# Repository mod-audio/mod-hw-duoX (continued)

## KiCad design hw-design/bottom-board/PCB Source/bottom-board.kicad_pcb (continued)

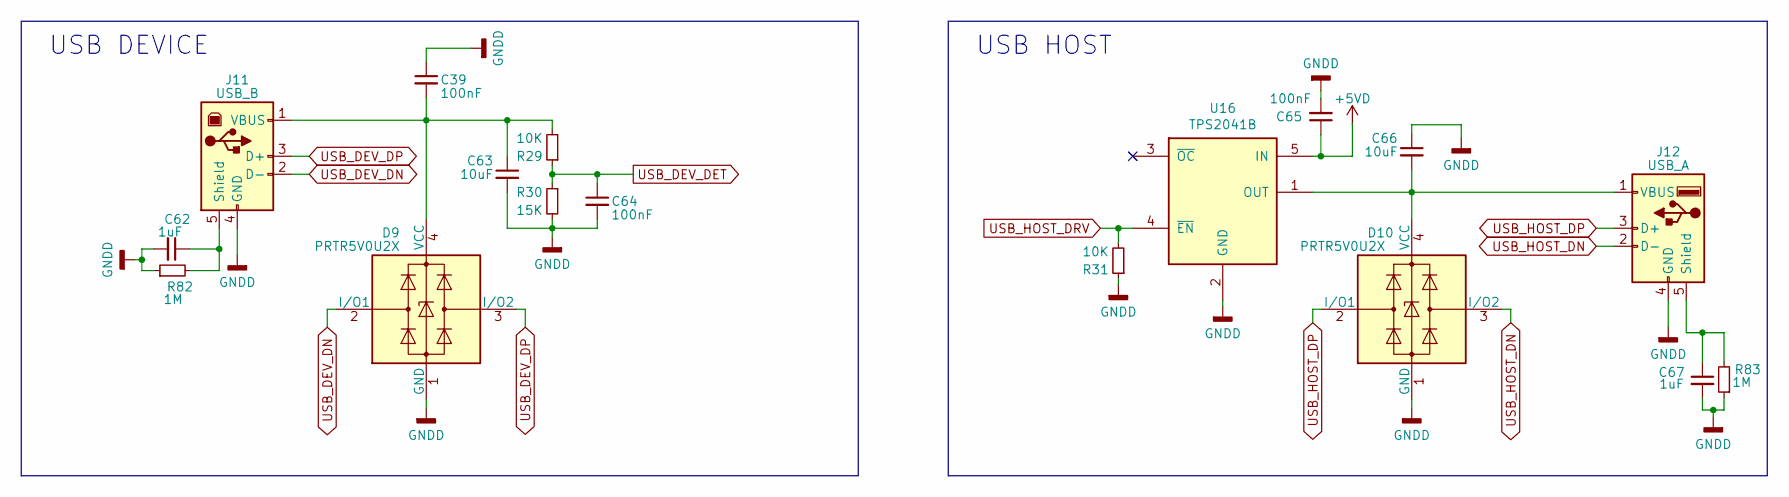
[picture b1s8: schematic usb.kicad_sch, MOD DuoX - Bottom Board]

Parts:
C39, C64, C65: 100nF; C_0603_1608Metric; MPN GCM188R71C104KA37D
C62, C67: 1uF; C_0603_1608Metric; MPN TMK107B7105KA-T
C63, C66: 10uF; C_0805_2012Metric; MPN GRM219R61E106KA12D
D9, D10: PRTR5V0U2X; SOT-143; MPN PRTR5V0U2X,215
J11: USB_B; USB_B_OST_USB-B1HSxx_Horizontal; MPN 61729-1011BLF
J12: USB_A; USB_A_Vertical; MPN KUSBX-SLAS1N-B
R29, R31: 10K; R_0603_1608Metric; MPN RR0816P-103-D
R30: 15K; R_0603_1608Metric; MPN RMCF0603JT15K0
R82, R83: 1M; R_0603_1608Metric; MPN RT0603BRD071ML
U16: TPS2041B; SOT-23-5

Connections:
+5VD: C65.1, U16.5 (IN); also elsewhere on the board
GNDD: C39.1, C62.2, C63.2, C64.2, C65.2, C66.1, C67.2, D9.1 (GND), D10.1 (GND), J11.4 (GND), J12.4 (GND), R30.2, R31.1, R82.1, R83.1, U16.2 (GND); also elsewhere on the board
unnamed: C39.2, C63.1, D9.4 (VCC), J11.1 (VBUS), R29.2
unnamed: C62.1, J11.5 (Shield), R82.2
unnamed: C66.2, D10.4 (VCC), J12.1 (VBUS), U16.1 (OUT)
unnamed: C67.1, J12.5 (Shield), R83.2
USB_DEV_DET: C64.1, R29.1, R30.1; also elsewhere on the board
USB_DEV_DN: D9.2 (I/O1), J11.2 (D-); also elsewhere on the board
USB_DEV_DP: D9.3 (I/O2), J11.3 (D+); also elsewhere on the board
USB_HOST_DN: D10.3 (I/O2), J12.2 (D-); also elsewhere on the board
USB_HOST_DP: D10.2 (I/O1), J12.3 (D+); also elsewhere on the board
USB_HOST_DRV: R31.2, U16.4 (~EN); also elsewhere on the board

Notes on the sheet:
USB DEVICE
USB HOST

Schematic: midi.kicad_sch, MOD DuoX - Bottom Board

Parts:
C68: 100nF; C_0603_1608Metric; MPN GCM188R71C104KA37D
D11, D12: 1N4148; D_SOD-323; MPN 1N4148WX-TP
D28: BAT54S; SOT-23; MPN BAT54SFILM
J13, J14: DIN_5; SDS-50J; MPN SDS-50J
Q3, Q4: 2N7002; SOT-23; MPN 2N7002P,215
R32, R33, R34: 220R; R_0603_1608Metric; MPN RC0603FR-07220RL
R35, R36: 10K; R_0603_1608Metric; MPN RR0816P-103-D
U17: 6N136S; SMDIP-8_W9.53mm; MPN 6N136S

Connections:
+5VD: C68.2, D28.2, R33.2, R35.1, R36.1, U17.8; also elsewhere on the board
GNDD: C68.1, D28.1, J14.2, Q3.2 (S), Q4.2 (S), U17.5; also elsewhere on the board
MIDI_UART_RX: D12.2 (A); also elsewhere on the board
MIDI_UART_TX: Q4.1 (G); also elsewhere on the board
unnamed: D11.1 (K), R32.2, U17.2
unnamed: D11.2 (A), J13.5, U17.3
unnamed: D12.1 (K), U17.6
unnamed: D28.3, J14.5, R34.1
unnamed: J13.4, R32.1
unnamed: J14.4, R33.1
unnamed: Q3.1 (G), Q4.3 (D), R36.2
unnamed: Q3.3 (D), R34.2, R35.2

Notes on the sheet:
MIDI IN
MIDI OUT
Opto: If = 16mA, Vf = 1.4V

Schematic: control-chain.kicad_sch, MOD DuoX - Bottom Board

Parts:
C69: 10uF; C_0805_2012Metric; MPN GRM219R61E106KA12D
C70, C71: 100nF; C_0603_1608Metric; MPN GCM188R71C104KA37D
J4: RJ45; Ethernet_Jack_54602-908LF; MPN 54602-908LF
R37, R38: 22R; R_0603_1608Metric; MPN RMCF0603JT22R0
R39, R40: 10K; R_0603_1608Metric; MPN RR0816P-103-D
R43, R44, R45, R46: 56R; R_0603_1608Metric; MPN CRGCQ0603F56R
R47: 100R; R_0603_1608Metric; MPN RT0603DRD07100RL
U18: ISL83086E; SOIC-14_3.9x8.7mm_P1.27mm; MPN ISL83491IBZ

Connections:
+5VD: C71.1, R39.1, U18.13 (VCC), U18.14 (VCC); also elsewhere on the board
+12V: C69.1, C70.1, J4.4, J4.5; also elsewhere on the board
CHAIN_UART_DE: R40.1, U18.4 (DE); also elsewhere on the board
CHAIN_UART_RE: R39.2, U18.3 (~RE); also elsewhere on the board
CHAIN_UART_RX: R38.1; also elsewhere on the board
CHAIN_UART_TX: R37.1; also elsewhere on the board
GNDD: C69.2, C70.2, C71.2, J4.7, J4.8, R40.2, U18.6 (GND), U18.7 (GND); also elsewhere on the board
unnamed: R37.2, U18.5 (DI)
unnamed: R38.2, U18.2 (RO)
unnamed: R43.2, U18.12 (A)
unnamed: R44.2, U18.11 (~B)
unnamed: R45.2, U18.9 (Y)
unnamed: R46.2, U18.10 (~Z)
RS485_RX+: J4.3, R43.1, R47.1
RS485_RX-: J4.6, R44.1, R47.2
RS485_TX+: J4.1, R45.1
RS485_TX-: J4.2, R46.1

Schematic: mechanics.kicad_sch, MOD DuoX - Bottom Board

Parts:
FID1, FID2, FID3: FIDUCIAL; fiducial_in-circuit
H1, H2, H3, H4, H5: HOLE; MountingHole_3.5mm
H6, H7: Standoff; MountingHole_3.2mm_M3_DIN965_Pad; MPN 9774030243R
H8, H9: HOLE; MountingHole_2.7mm
IMG1: Logo; mod-logo

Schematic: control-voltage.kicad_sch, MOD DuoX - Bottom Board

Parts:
C34, C35, C76, C81: 10uF; C_0805_2012Metric; MPN GRM219R61E106KA12D
C73, C74: 33nF; C_0603_1608Metric; MPN C0603C333K4RACTU
C75, C80, C82, C83: 100nF; C_0603_1608Metric; MPN GCM188R71C104KA37D
C77: 1uF; C_0603_1608Metric; MPN TMK107B7105KA-T
D13, D20: 1N4148; D_SOD-323; MPN 1N4148WX-TP
D14, D15: BAT54S; SOT-23; MPN BAT54SFILM
J16, J17: NYS215; NMJ6HCD2; MPN NYS215
R48, R50, R51, R52, R79, R80, R133, R134, R135, R136, R137, R138, R139, R140: 10K; R_0603_1608Metric; MPN RR0816P-103-D
R85: 56K; R_0603_1608Metric; MPN RT0603DRD0756KL
R86: 100K; R_0603_1608Metric; MPN RMCF0603JT100K
R87: 220K; R_0603_1608Metric; MPN RMCF0603JT220K
R88: 47K; R_0603_1608Metric; MPN RMCF0603JT47K0
R89, R90: 15K; R_0603_1608Metric; MPN RMCF0603JT15K0
R141, R142: 499K; R_0603_1608Metric; MPN ERJ-3EKF4993V
R143, R144: 1K; R_0603_1608Metric; MPN ERJ-PB3D1001V
TP14, TP15, TP16: TestPoint; TestPoint_Pad_D1.0mm
U3: 74LVC3G17; VSSOP-8_2.3x2mm_P0.5mm; MPN SN74LVC3G17DCUR
U4: LD1117S50TR; SOT-223-3_TabPin2; MPN LD1117S50TR
U9: DG9426E; TSSOP-16_4.4x5mm_P0.65mm
U10: LM358; TSSOP-8_3x3mm_P0.65mm; MPN TLV272CM8-13
U13: DG9426E; TSSOP-16_4.4x5mm_P0.65mm; MPN DG9426EDQ-T1-GE3
U20: ADC122S021; VSSOP-8_3.0x3.0mm_P0.65mm; MPN ADC122S021CIMM/NOPB
U21: MIC2076A; SOIC-8_3.9x4.9mm_P1.27mm; MPN MIC2076A-1YM
U24: MCP4922-EP; SOIC-14_3.9x8.7mm_P1.27mm; MPN MCP4922T-E/SL

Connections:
+5VA: C80.2, C81.1, C82.2, C83.2, R141.1, R142.1, U3.8 (VCC), U13.12 (VL), U24.1 (VDD), U24.9 (~SHDN), U24.11 (VrefB), U24.13 (VrefA); also elsewhere on the board
+5VP: C35.1, C75.2, C76.1, C77.2, D14.2, D15.2, R79.2, R80.2, R86.2, U4.2 (VO), U9.12 (VL), U20.2 (VA), U21.7 (IN); also elsewhere on the board
CV1_IN: J16.T, R133.1, U9.14, U21.8 (OUTA)
CV2_IN: J16.R, R134.1, U9.11, U21.5 (OUTB)
CV_10V_OUT1: R139.2, U10.1, U13.11
CV_10V_OUT2: R140.2, U10.7, U13.15
CV_ADC_DIN: U3.1, U20.6 (DIN); also elsewhere on the board
CV_ADC_DOUT: U20.7 (DOUT); also elsewhere on the board
CV_ADC_SCLK: U3.3, U20.8 (SCLK); also elsewhere on the board
CV_ADC_~CS~: TP16.1, U20.1 (~CS); also elsewhere on the board
CV_DAC_~CS~: U3.6; also elsewhere on the board
CV_EXP_SW: D13.1 (K), D20.1 (K), R48.1, U9.1, U9.8, U9.9, U9.16
CV_IN_DET: J16.SN, R85.2, R86.1; also elsewhere on the board
CV_OUT_1: R143.2, U10.3 (+)
CV_OUT_2: R144.2, U10.5 (+)
CV_OUT_DET: J17.SN, R87.1, R88.2; also elsewhere on the board
EXP_EN1: D13.2 (A), R51.1, TP15.1, U21.1 (ENA); also elsewhere on the board
EXP_EN2: D20.2 (A), R50.1, TP14.1, U21.4 (ENB); also elsewhere on the board
EXP_FLAG1: R80.1, R89.2, U21.2 (FLGA); also elsewhere on the board
EXP_FLAG2: R79.1, R90.2, U21.3 (FLGB); also elsewhere on the board
GNDD: C77.1, R48.2, R50.2, R51.2, R52.2, R85.1, R88.1, R89.1, R90.1, R135.2, R136.2, U9.4 (V-), U9.5 (GND), U13.4 (V-), U13.5 (GND), U21.6 (GND); also elsewhere on the board
HP_CV_JACK_RING: J17.R, U13.6, U13.14
HP_CV_JACK_TIP: J17.T, U13.3, U13.10
HP_DISABLE: R52.1, U13.1, U13.8, U13.9, U13.16; also elsewhere on the board
HP_LEFT: U13.2; also elsewhere on the board
HP_RIGHT: U13.7; also elsewhere on the board
unnamed: C73.1, D15.3, U9.2, U9.15, U20.5 (IN1)
unnamed: C74.1, D14.3, U9.7, U9.10, U20.4 (IN2)
unnamed: R133.2, R135.1, U9.3
unnamed: R134.2, R136.1, U9.6
unnamed: R137.2, R139.1, U10.2 (-)
unnamed: R138.2, R140.1, U10.6 (-)
unnamed: R141.2, R143.1, U24.14 (VoutA)
unnamed: R142.2, R144.1, U24.10 (VoutB)
unnamed: U3.2, U24.3 (~CS)
unnamed: U3.5, U24.4 (SCK)
unnamed: U3.7, U24.5 (SDI)

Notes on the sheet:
Overcurrent flag pullup
CV INPUT
DAC outputs have Hi-Z (500k) when shutdown is on
Exp. Pedal Enable
Amplify the signel by a factor of 2, to scale back to the 0 to 10V range Needs to be rail to rail with 10V as supply
MIC2076A outputs have Hi-Z when disabled
CV OUTPUT

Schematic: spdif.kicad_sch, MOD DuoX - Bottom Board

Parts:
C84: 10nF; C_0603_1608Metric; MPN CL10B103KA8NNNC
C85: 22pF; C_0603_1608Metric; MPN C0603C220K4GACTU
J18: MJ-3536N; MPN MJ-3536N
R55: 243R; R_0603_1608Metric; MPN RC0603FR-07243RL
R56: 107R; R_0603_1608Metric; MPN RC0603FR-07107RL
TR1: Transformer_1P_1S_SO8; PE-65812NL; MPN PE-65812NL

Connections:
CODEC_SPDIF_OUT: C84.2; also elsewhere on the board
GNDD: C85.1, R56.2, TR1.4 (AB); also elsewhere on the board
unnamed: C84.1, R55.2
unnamed: C85.2, J18.S, TR1.5 (SA)
unnamed: J18.T, TR1.8 (SB)
unnamed: R55.1, R56.1, TR1.1 (AA)

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
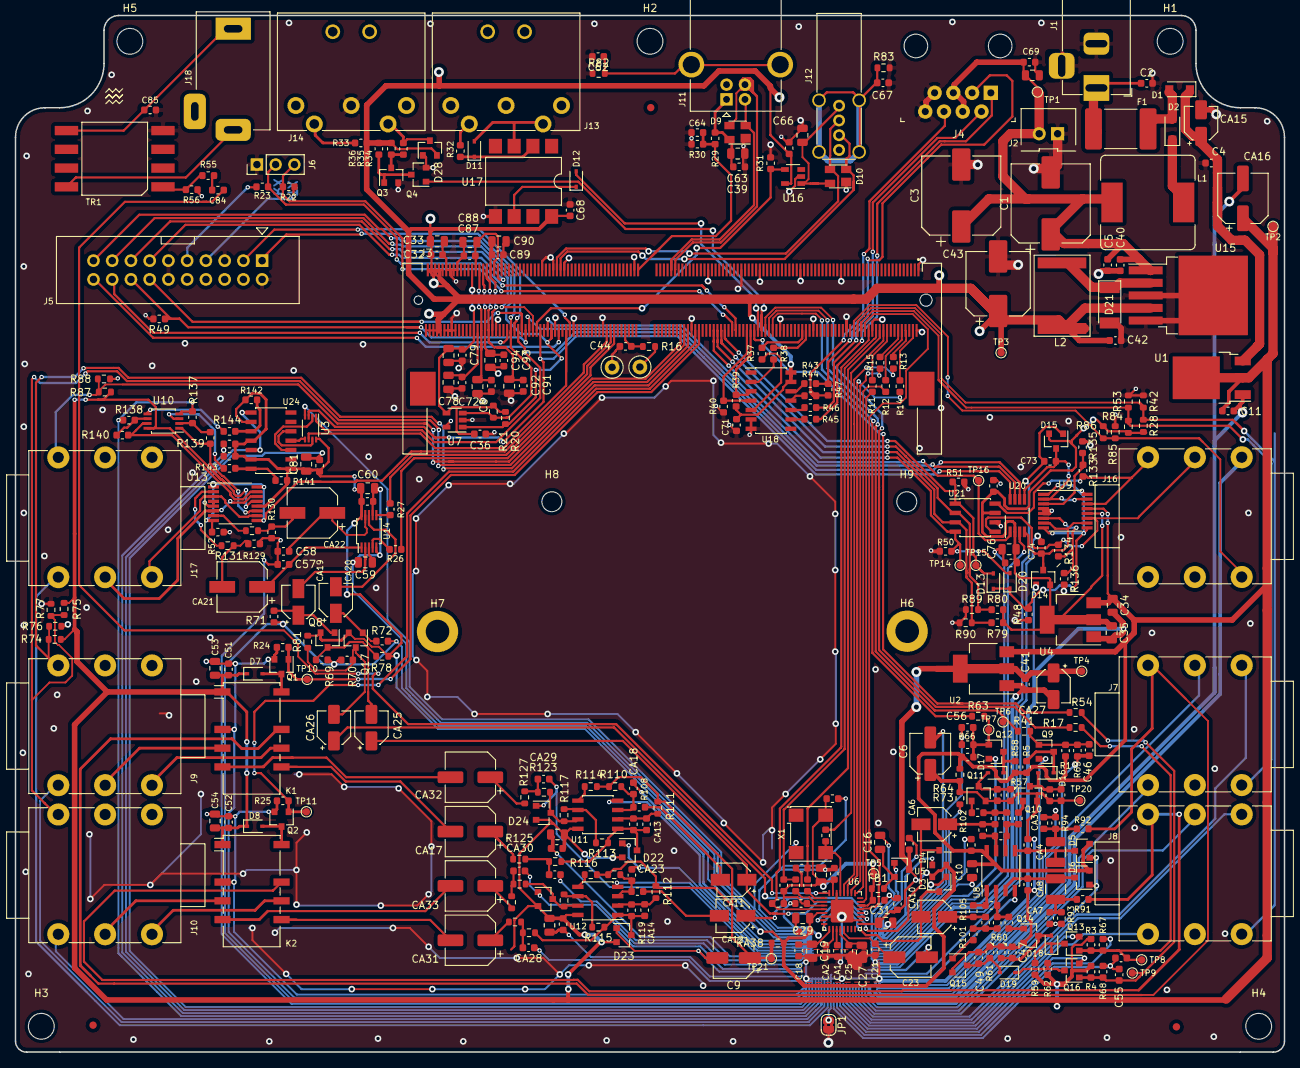
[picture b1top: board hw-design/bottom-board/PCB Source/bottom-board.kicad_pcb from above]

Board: 4 copper layers, 172.0 x 140.5 mm, 390 parts (1 on the bottom side), 227 nets.

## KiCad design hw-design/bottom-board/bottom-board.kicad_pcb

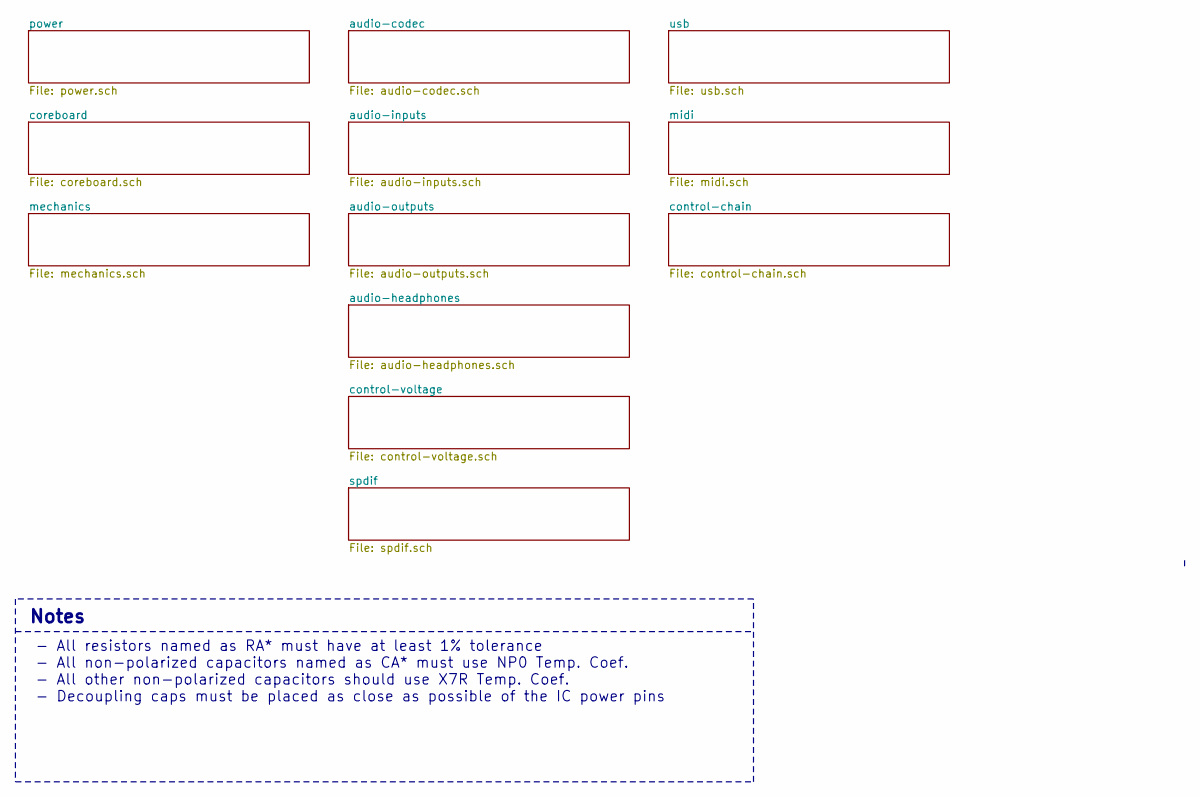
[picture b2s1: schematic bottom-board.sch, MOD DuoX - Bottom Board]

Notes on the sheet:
- All resistors named as RA* must have at least 1% tolerance - All non-polarized capacitors named as CA* must use NP0 Temp. Coef. - All other non-polarized capacitors should use X7R Temp. Coef. - Decoupling caps must be placed as close as possible of the IC power pins
Notes

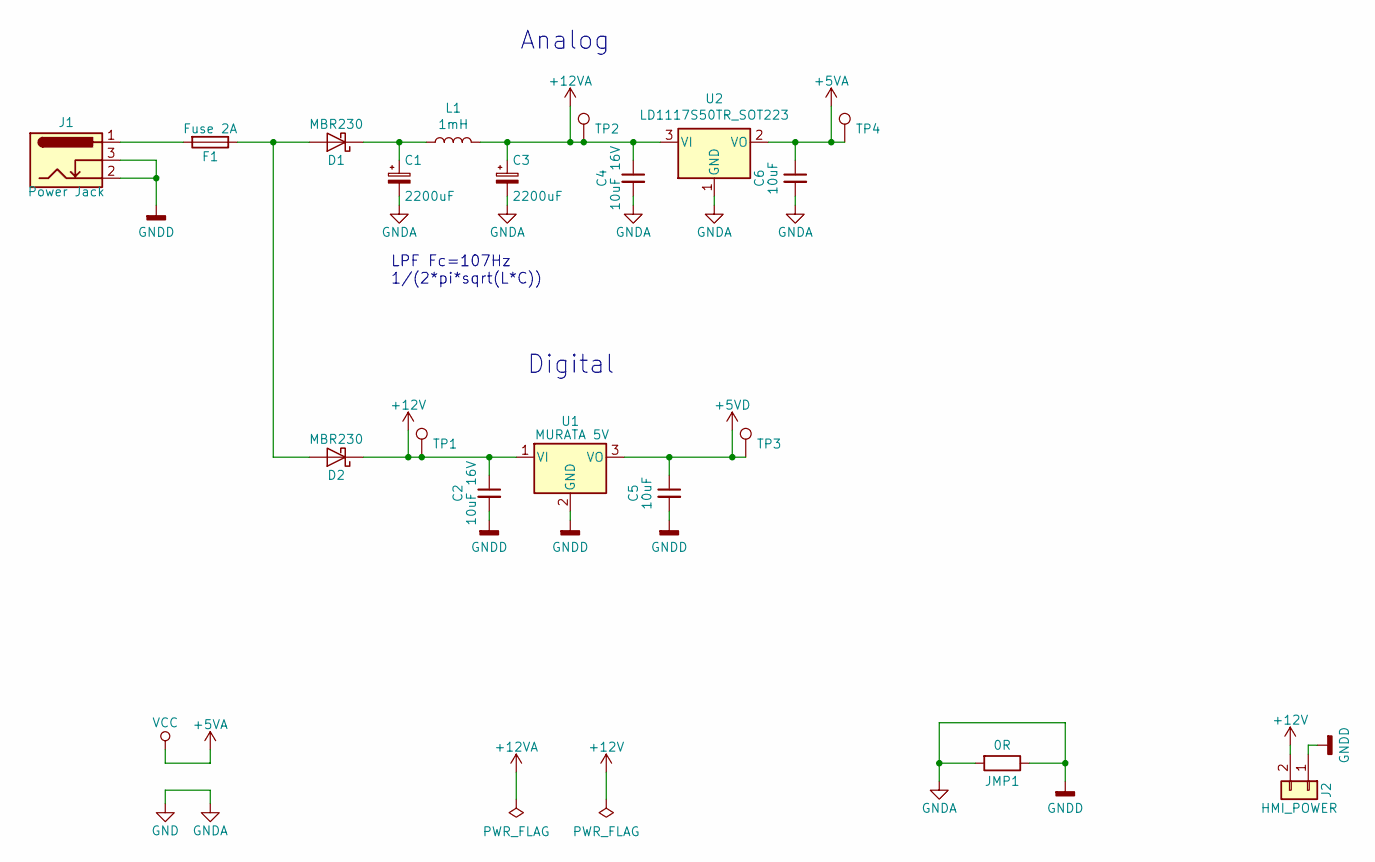
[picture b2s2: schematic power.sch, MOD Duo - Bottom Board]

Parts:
C1, C3: 2200uF; CP_Radial_D13.0mm_P5.00mm; MPN ESK228M025AL4AA
C2, C4: 10uF 16V; C_0805_2012Metric; MPN CL21A106KOFNNNE
C5, C6: 10uF; C_0603_1608Metric; MPN CL10A106MQ8NNNC
D1, D2: MBR230; D_SOD-123F; MPN MBR230LSFT1G
F1: Fuse 2A; Fuse_2920_0ZCF_Bel; MPN 0ZCF0200FF2C
J1: Power Jack; BarrelJack_Horizontal; MPN PJ-002AH
J2: HMI_POWER; B2B-XH-A; MPN B2B-XH-A(LF)(SN)
JMP1: 0R; Jumper_SMD_THT
L1: 1mH; L_Bourns_SRR1260; MPN SRR1260-102K
TP1, TP2, TP3, TP4: TestPoint; TestPoint_Pad_D1.0mm
U1: MURATA 5V; OKI-78SR_Vertical; MPN OKI-78SR-5/1.5-W36-C
U2: LD1117S50TR_SOT223; SOT-223-3_TabPin2; MPN LD1117S50TR

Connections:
+5VD: C5.1, TP3.1, U1.3 (VO); also elsewhere on the board
+12V: C2.1, D2.1 (K), J2.2, TP1.1, U1.1 (VI); also elsewhere on the board
+12VA: C3.1, C4.1, L1.2, TP2.1, U2.3 (VI); also elsewhere on the board
unnamed: C1.1, D1.1 (K), L1.1
unnamed: D1.2 (A), D2.2 (A), F1.1
unnamed: F1.2, J1.1

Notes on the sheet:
Analog
Digital
LPF Fc=107Hz 1/(2*pi*sqrt(L*C))

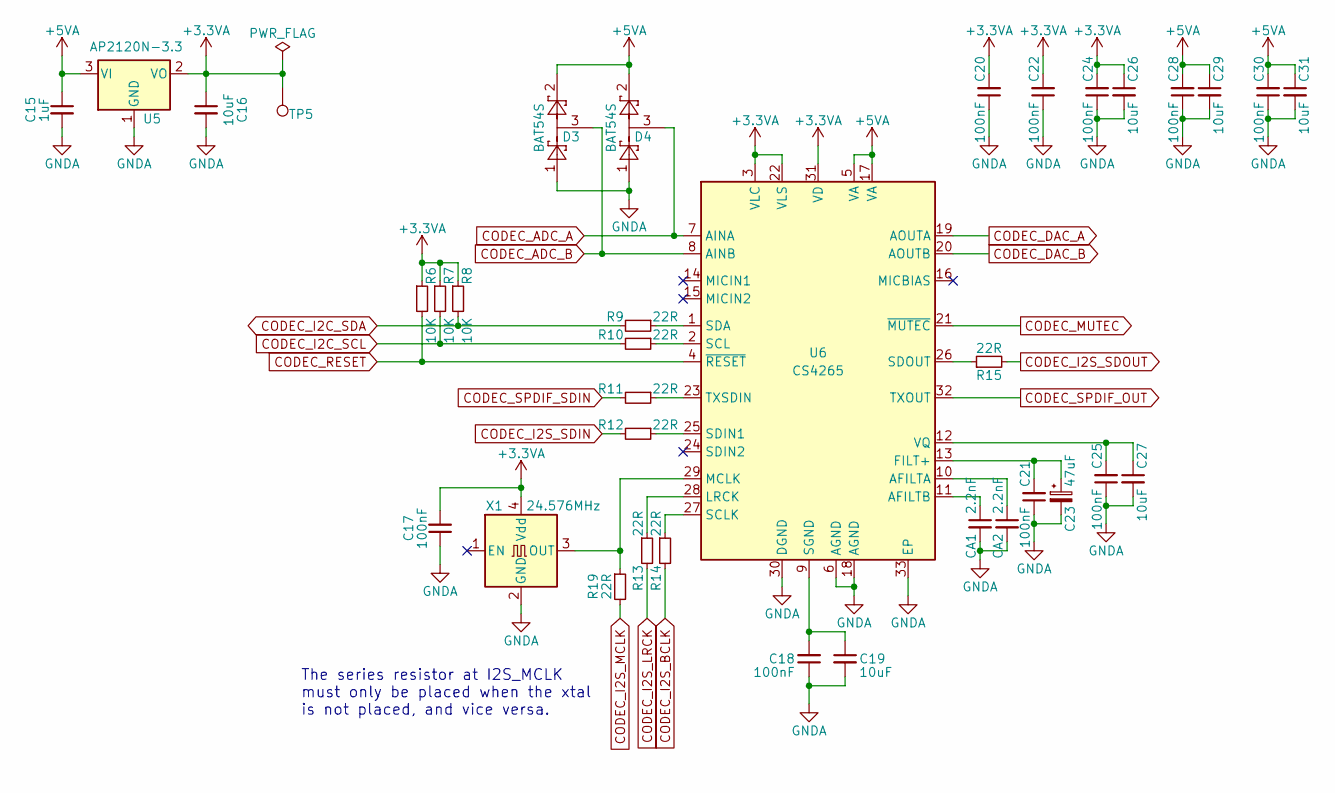
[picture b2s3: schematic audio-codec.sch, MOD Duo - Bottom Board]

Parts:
C15: 1uF; C_0603_1608Metric; MPN CL10B105KP8NNNC
C16, C19, C26, C27, C29, C31: 10uF; C_0603_1608Metric; MPN CL10A106MQ8NNNC
C17, C18, C20, C21, C22, C24, C25, C28, C30: 100nF; C_0603_1608Metric; MPN GCM188R71C104KA37D
C23: 47uF; CP_Elec_5x5.4; MPN EDK476M016A9DAA
CA1, CA2: 2.2nF; C_0603_1608Metric; MPN GRM1885C1H222JA01D
D3, D4: BAT54S; SOT-23; MPN BAT54SFILM
R6, R7, R8: 10K; R_0603_1608Metric; MPN RR0816P-103-D
R9, R10, R11, R12, R13, R14, R15: 22R; R_0603_1608Metric; MPN RMCF0603JT22R0
R19: 22R; R_0603_1608Metric; MPN DO NOT PLACE
TP5: TestPoint; TestPoint_Pad_D1.0mm
U5: AP2120N-3.3; SOT-23; MPN AP2120N-3.3TRG1
U6: CS4265; QFN-32-1EP_5x5mm_P0.5mm_EP3.1x3.1mm; MPN CS4265-CNZ
X1: 24.576MHz; Oscillator_SMD_Abracon_ASV-4Pin_7.0x5.1mm; MPN ASV-24.576MHZ-EJ-T

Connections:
+3.3VA: C16.1, C17.2, C20.2, C22.2, C24.2, C26.1, R6.1, R7.1, R8.1, TP5.1, U5.2 (VO), U6.3 (VLC), U6.22 (VLS), U6.31 (VD), X1.4 (Vdd)
CODEC_ADC_A: D4.3, U6.7 (AINA); also elsewhere on the board
CODEC_ADC_B: D3.3, U6.8 (AINB); also elsewhere on the board
CODEC_DAC_A: U6.19 (AOUTA); also elsewhere on the board
CODEC_DAC_B: U6.20 (AOUTB); also elsewhere on the board
CODEC_I2C_SCL: R7.2, R10.2; also elsewhere on the board
CODEC_I2C_SDA: R8.2, R9.2; also elsewhere on the board
CODEC_I2S_BCLK: R14.2; also elsewhere on the board
CODEC_I2S_LRCK: R13.2; also elsewhere on the board
CODEC_I2S_MCLK: R19.2; also elsewhere on the board
CODEC_I2S_SDIN: R12.2; also elsewhere on the board
CODEC_I2S_SDOUT: R15.2; also elsewhere on the board
CODEC_MUTEC: U6.21 (~MUTEC); also elsewhere on the board
CODEC_RESET: R6.2, U6.4 (~RESET); also elsewhere on the board
CODEC_SPDIF_OUT: U6.32 (TXOUT); also elsewhere on the board
CODEC_SPDIF_SDIN: R11.2; also elsewhere on the board
unnamed: C18.2, C19.1, U6.9 (SGND)
unnamed: C21.2, C23.1, U6.13 (FILT+)
unnamed: C25.2, C27.1, U6.12 (VQ)
unnamed: CA1.1, U6.11 (AFILTB)
unnamed: CA2.1, U6.10 (AFILTA)
unnamed: R9.1, U6.1 (SDA)
unnamed: R10.1, U6.2 (SCL)
unnamed: R11.1, U6.23 (TXSDIN)
unnamed: R12.1, U6.25 (SDIN1)
unnamed: R13.1, U6.28 (LRCK)
unnamed: R14.1, U6.27 (SCLK)
unnamed: R15.1, U6.26 (SDOUT)
unnamed: R19.1, U6.29 (MCLK), X1.3 (OUT)

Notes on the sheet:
The series resistor at I2S_MCLK must only be placed when the xtal is not placed, and vice versa.

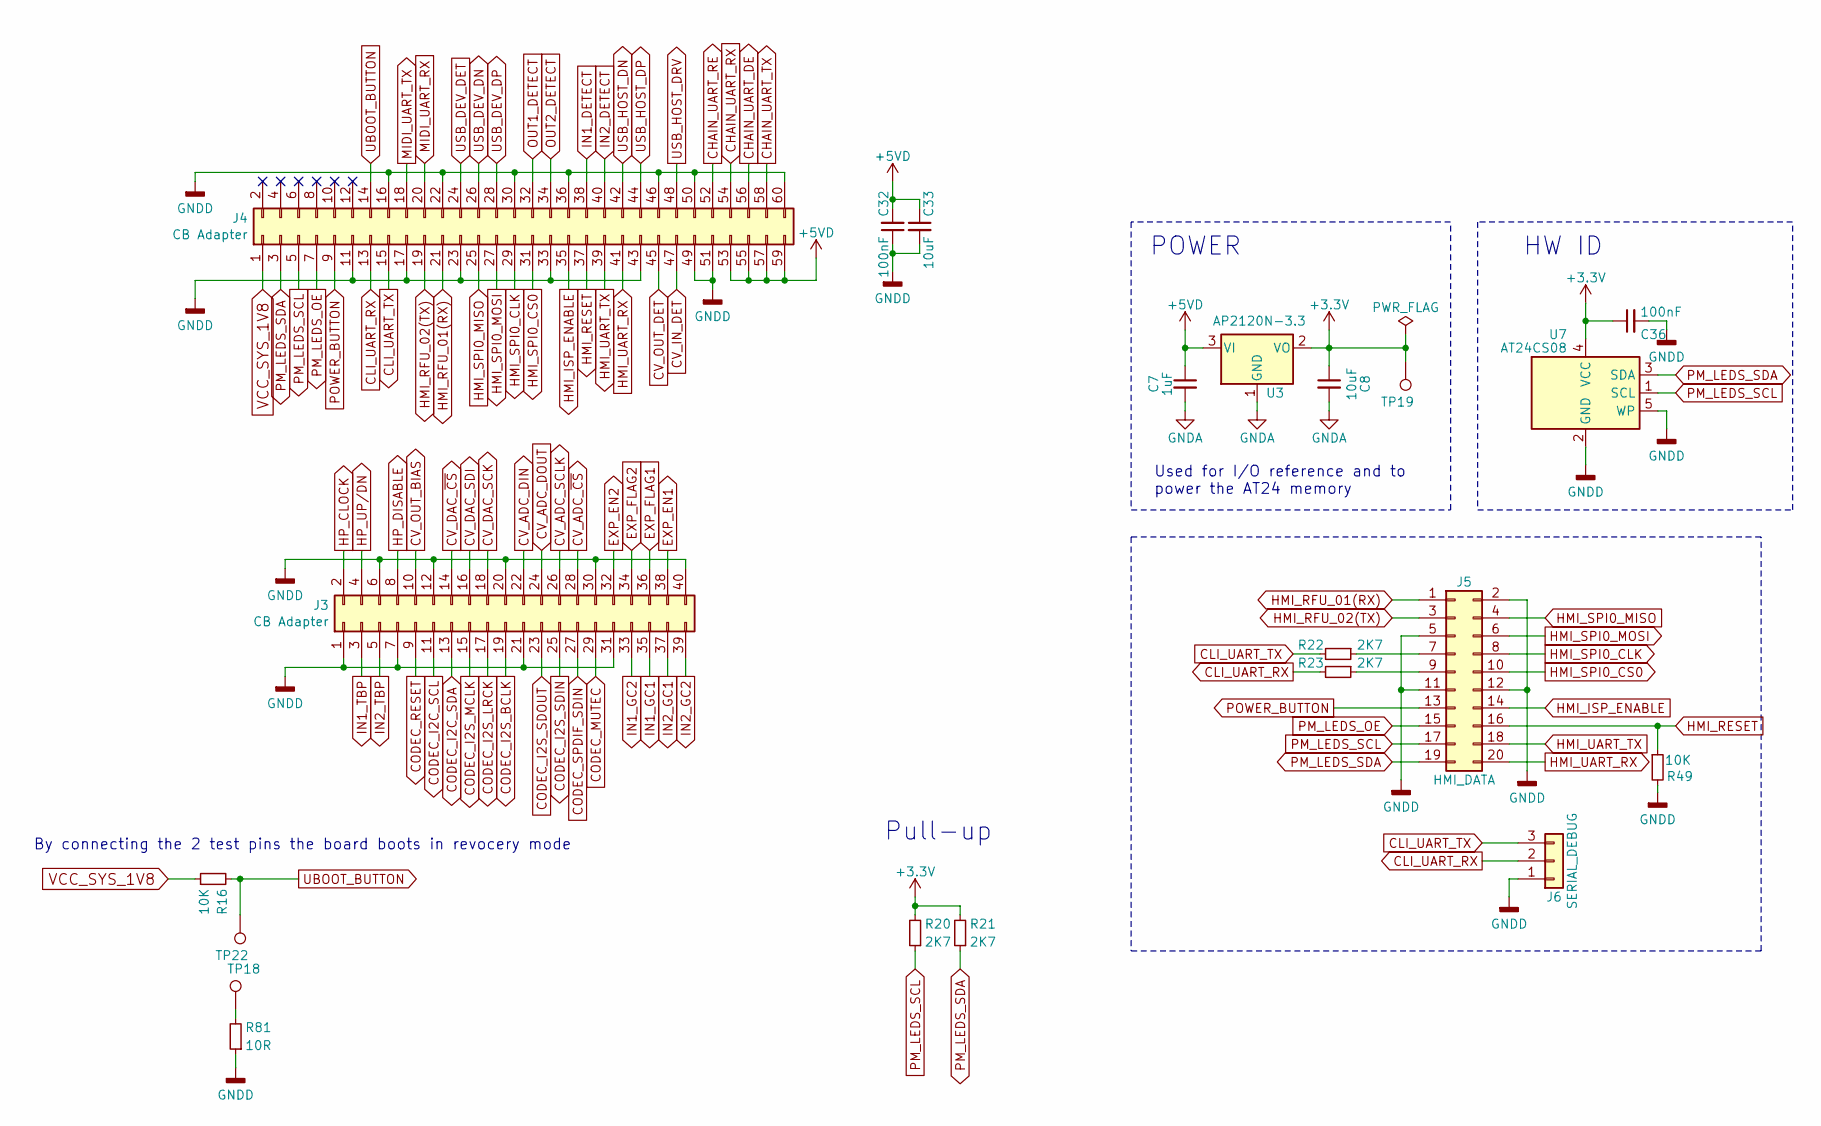
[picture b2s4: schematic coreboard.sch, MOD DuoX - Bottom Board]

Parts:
C7: 1uF; C_0603_1608Metric; MPN CL10B105KP8NNNC
C8, C33: 10uF; C_0603_1608Metric; MPN CL10A106MQ8NNNC
C32, C36: 100nF; C_0603_1608Metric; MPN GCM188R71C104KA37D
J3: CB Adapter; DF12(3.0)-40DP-0.5V(86); MPN DF12(3.0)-40DP-0.5V(86)
J4: CB Adapter; DF12(3.0)-60DP-0.5V(86); MPN DF12(3.0)-60DP-0.5V(86)
J5: HMI_DATA; Pin_Header_Straight_2x10_Shrouded; MPN 302-S201
J6: SERIAL_DEBUG; PinHeader_1x03_P2.54mm_Vertical; MPN DO NOT PLACE
R16, R49: 10K; R_0603_1608Metric; MPN RR0816P-103-D
R20, R21, R22, R23: 2K7; R_0603_1608Metric; MPN RMCF0603JT2K70
R81: 10R; R_0603_1608Metric; MPN CRGCQ0603J10R
TP18, TP19, TP22: TestPoint; TestPoint_Pad_D1.0mm
U3: AP2120N-3.3; SOT-23; MPN AP2120N-3.3TRG1
U7: AT24CS08; SOT-23-5; MPN AT24CS08-STUM-T

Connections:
+3V3: C8.1, C36.1, R20.2, R21.2, TP19.1, U3.2 (VO), U7.4 (VCC)
+5VD: C7.1, C32.2, C33.1, J4.53, J4.55, J4.57, J4.59, U3.3 (VI); also elsewhere on the board
CHAIN_UART_DE: J4.56; also elsewhere on the board
CHAIN_UART_RE: J4.52; also elsewhere on the board
CHAIN_UART_RX: J4.54; also elsewhere on the board
CHAIN_UART_TX: J4.58; also elsewhere on the board
CLI_UART_RX: J4.13, J6.2, R23.2; also elsewhere on the board
CLI_UART_TX: J4.15, J6.3, R22.2; also elsewhere on the board
CODEC_I2C_SCL: J3.11; also elsewhere on the board
CODEC_I2C_SDA: J3.13; also elsewhere on the board
CODEC_I2S_BCLK: J3.19; also elsewhere on the board
CODEC_I2S_LRCK: J3.17; also elsewhere on the board
CODEC_I2S_MCLK: J3.15; also elsewhere on the board
CODEC_I2S_SDIN: J3.25; also elsewhere on the board
CODEC_I2S_SDOUT: J3.23; also elsewhere on the board
CODEC_MUTEC: J3.29; also elsewhere on the board
CODEC_RESET: J3.9; also elsewhere on the board
CODEC_SPDIF_SDIN: J3.27; also elsewhere on the board
CV_ADC_DIN: J3.22; also elsewhere on the board
CV_ADC_DOUT: J3.24; also elsewhere on the board
CV_ADC_SCLK: J3.26; also elsewhere on the board
CV_ADC_~CS~: J3.28; also elsewhere on the board
CV_DAC_SCK: J3.18; also elsewhere on the board
CV_DAC_SDI: J3.16; also elsewhere on the board
CV_DAC_~CS~: J3.14; also elsewhere on the board
CV_IN_DET: J4.47; also elsewhere on the board
CV_OUT_DET: J4.45; also elsewhere on the board
EXP_FLAG1: J3.36; also elsewhere on the board
EXP_FLAG2: J3.34; also elsewhere on the board
HMI_ISP_ENABLE: J4.35, J5.14
HMI_RESET: J4.37, J5.16, R49.1
HMI_RFU_01(RX): J4.21, J5.1
HMI_RFU_02(TX): J4.19, J5.3
HMI_SPI0_CLK: J4.29, J5.8
HMI_SPI0_CS0: J4.31, J5.10
HMI_SPI0_MISO: J4.25, J5.4
HMI_SPI0_MOSI: J4.27, J5.6
HMI_UART_RX: J4.41, J5.20
HMI_UART_TX: J4.39, J5.18
HP_CLOCK: J3.2; also elsewhere on the board
HP_DISABLE: J3.8; also elsewhere on the board
HP_UP/DN: J3.4; also elsewhere on the board
IN1_DETECT: J4.38; also elsewhere on the board
IN1_GC1: J3.35; also elsewhere on the board
IN1_GC2: J3.33; also elsewhere on the board
IN1_TBP: J3.3; also elsewhere on the board
IN2_DETECT: J4.40; also elsewhere on the board
IN2_GC1: J3.37; also elsewhere on the board
IN2_GC2: J3.39; also elsewhere on the board
IN2_TBP: J3.5; also elsewhere on the board
MIDI_UART_RX: J4.20; also elsewhere on the board
MIDI_UART_TX: J4.18; also elsewhere on the board
unnamed: J5.7, R22.1
unnamed: J5.9, R23.1
unnamed: R81.2, TP18.1
OUT1_DETECT: J4.32; also elsewhere on the board
OUT2_DETECT: J4.34; also elsewhere on the board
PM_LEDS_OE: J4.7, J5.15
PM_LEDS_SCL: J4.5, J5.17, R20.1, U7.1 (SCL)
PM_LEDS_SDA: J4.3, J5.19, R21.1, U7.3 (SDA)
POWER_BUTTON: J4.9, J5.13
UBOOT_BUTTON: J4.14, R16.2, TP22.1
USB_DEV_DET: J4.24; also elsewhere on the board
USB_DEV_DN: J4.26; also elsewhere on the board
USB_DEV_DP: J4.28; also elsewhere on the board
USB_HOST_DN: J4.42; also elsewhere on the board
USB_HOST_DP: J4.44; also elsewhere on the board
USB_HOST_DRV: J4.48; also elsewhere on the board
VCC_SYS_1V8: J4.1, R16.1

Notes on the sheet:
Pull-up
HW ID
POWER
Used for I/O reference and to power the AT24 memory
By connecting the 2 test pins the board boots in revocery mode

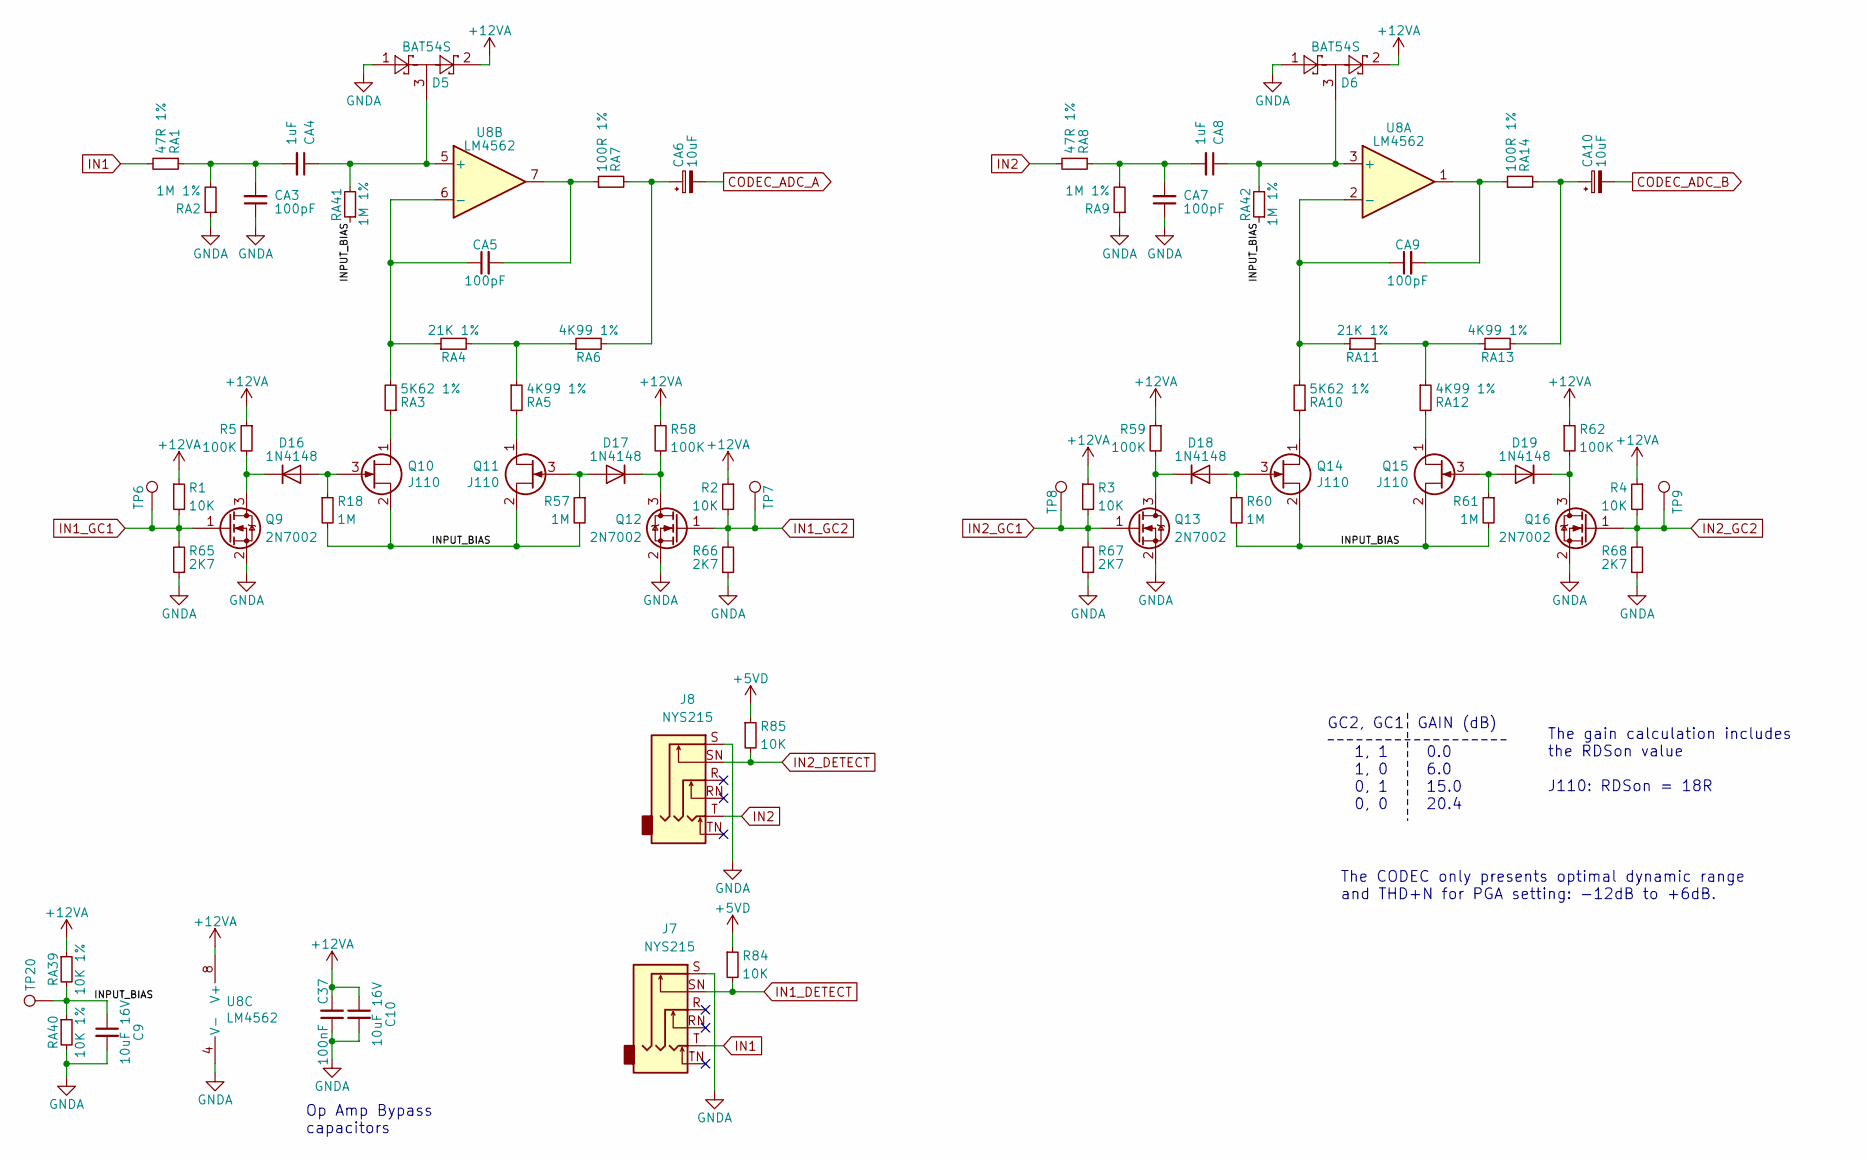
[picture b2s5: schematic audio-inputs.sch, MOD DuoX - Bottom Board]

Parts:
C9, C10: 10uF 16V; C_0805_2012Metric; MPN CL21A106KOFNNNE
C37: 100nF; C_0603_1608Metric; MPN GCM188R71C104KA37D
CA3, CA5, CA7, CA9: 100pF; C_0603_1608Metric; MPN C0603C101J3GACTU
CA4, CA8: 1uF; C_1210_3225Metric; MPN FCA1210C105M-G2
CA6, CA10: 10uF; CP_Elec_4x5.7; MPN EEE-HB1C100R
D5, D6: BAT54S; SOT-23; MPN BAT54SFILM
D16, D17, D18, D19: 1N4148; D_SOD-323; MPN 1N4148WX-TP
J7, J8: NYS215; NMJ6HCD2; MPN NYS215
Q9, Q12, Q13, Q16: 2N7002; SOT-23; MPN 2N7002P,215
Q10, Q11, Q14, Q15: J110; SOT-23; MPN PMBFJ110,215
R1, R2, R3, R4, R84, R85: 10K; R_0603_1608Metric; MPN RR0816P-103-D
R5, R58, R59, R62: 100K; R_0603_1608Metric; MPN RMCF0603JT100K
R18, R57, R60, R61: 1M; R_0603_1608Metric; MPN RT0603BRD071ML
R65, R66, R67, R68: 2K7; R_0603_1608Metric; MPN RMCF0603JT2K70
RA1, RA8: 47R 1%; R_0603_1608Metric; MPN RT0603DRE0747RL
RA2, RA9, RA41, RA42: 1M 1%; R_0603_1608Metric; MPN RT0603BRD071ML
RA3, RA10: 5K62 1%; R_0603_1608Metric; MPN ERA-3AEB5621V
RA4, RA11: 21K 1%; R_0603_1608Metric; MPN RR0816P-2102-D-32C
RA5, RA6, RA12, RA13: 4K99 1%; R_0603_1608Metric; MPN ERA-3AEB4991V
RA7, RA14: 100R 1%; R_0603_1608Metric; MPN RR0816P-101-D
RA39, RA40: 10K 1%; R_0603_1608Metric; MPN RR0816P-103-D
TP6, TP7, TP8, TP9, TP20: TestPoint; TestPoint_Pad_D1.0mm
U8: LM4562; SOIC-8_3.9x4.9mm_P1.27mm; MPN LM4562MAX/NOPB

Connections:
+5VD: R84.1, R85.1; also elsewhere on the board
+12VA: C10.1, C37.2, D5.2, D6.2, R1.1, R2.1, R3.1, R4.1, R5.1, R58.1, R59.1, R62.1, RA39.1, U8.8 (V+); also elsewhere on the board
/audio-inputs/INPUT_BIAS: C9.1, Q10.2 (S), Q11.2 (S), Q14.2 (S), Q15.2 (S), R18.2, R57.2, R60.2, R61.2, RA39.2, RA40.1, RA41.1, RA42.1, TP20.1
CODEC_ADC_A: CA6.2; also elsewhere on the board
CODEC_ADC_B: CA10.2; also elsewhere on the board
IN1: J7.T, RA1.2; also elsewhere on the board
IN1_DETECT: J7.SN, R84.2; also elsewhere on the board
IN1_GC1: Q9.1 (G), R1.2, R65.2, TP6.1; also elsewhere on the board
IN1_GC2: Q12.1 (G), R2.2, R66.2, TP7.1; also elsewhere on the board
IN2: J8.T, RA8.2; also elsewhere on the board
IN2_DETECT: J8.SN, R85.2; also elsewhere on the board
IN2_GC1: Q13.1 (G), R3.2, R67.2, TP8.1; also elsewhere on the board
IN2_GC2: Q16.1 (G), R4.2, R68.2, TP9.1; also elsewhere on the board
unnamed: CA3.2, CA4.2, RA1.1, RA2.2
unnamed: CA4.1, D5.3, RA41.2, U8.5 (+)
unnamed: CA5.1, RA3.2, RA4.1, U8.6 (-)
unnamed: CA5.2, RA7.1, U8.7
unnamed: CA6.1, RA6.2, RA7.2
unnamed: CA7.2, CA8.2, RA8.1, RA9.2
unnamed: CA8.1, D6.3, RA42.2, U8.3 (+)
unnamed: CA9.1, RA10.2, RA11.1, U8.2 (-)
unnamed: CA9.2, RA14.1, U8.1
unnamed: CA10.1, RA13.2, RA14.2
unnamed: D16.1 (K), Q9.3 (D), R5.2
unnamed: D16.2 (A), Q10.3 (G), R18.1
unnamed: D17.1 (K), Q12.3 (D), R58.2
unnamed: D17.2 (A), Q11.3 (G), R57.1
unnamed: D18.1 (K), Q13.3 (D), R59.2
unnamed: D18.2 (A), Q14.3 (G), R60.1
unnamed: D19.1 (K), Q16.3 (D), R62.2
unnamed: D19.2 (A), Q15.3 (G), R61.1
unnamed: Q10.1 (D), RA3.1
unnamed: Q11.1 (D), RA5.2
unnamed: Q14.1 (D), RA10.1
unnamed: Q15.1 (D), RA12.2
unnamed: RA4.2, RA5.1, RA6.1
unnamed: RA11.2, RA12.1, RA13.1

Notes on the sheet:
Op Amp Bypass capacitors
1, 1 1, 0 0, 1 0, 0
GAIN (dB)
GC2, GC1
0.0 6.0 15.0 20.4
The CODEC only presents optimal dynamic range and THD+N for PGA setting: -12dB to +6dB.
The gain calculation includes the RDSon value J110: RDSon = 18R
